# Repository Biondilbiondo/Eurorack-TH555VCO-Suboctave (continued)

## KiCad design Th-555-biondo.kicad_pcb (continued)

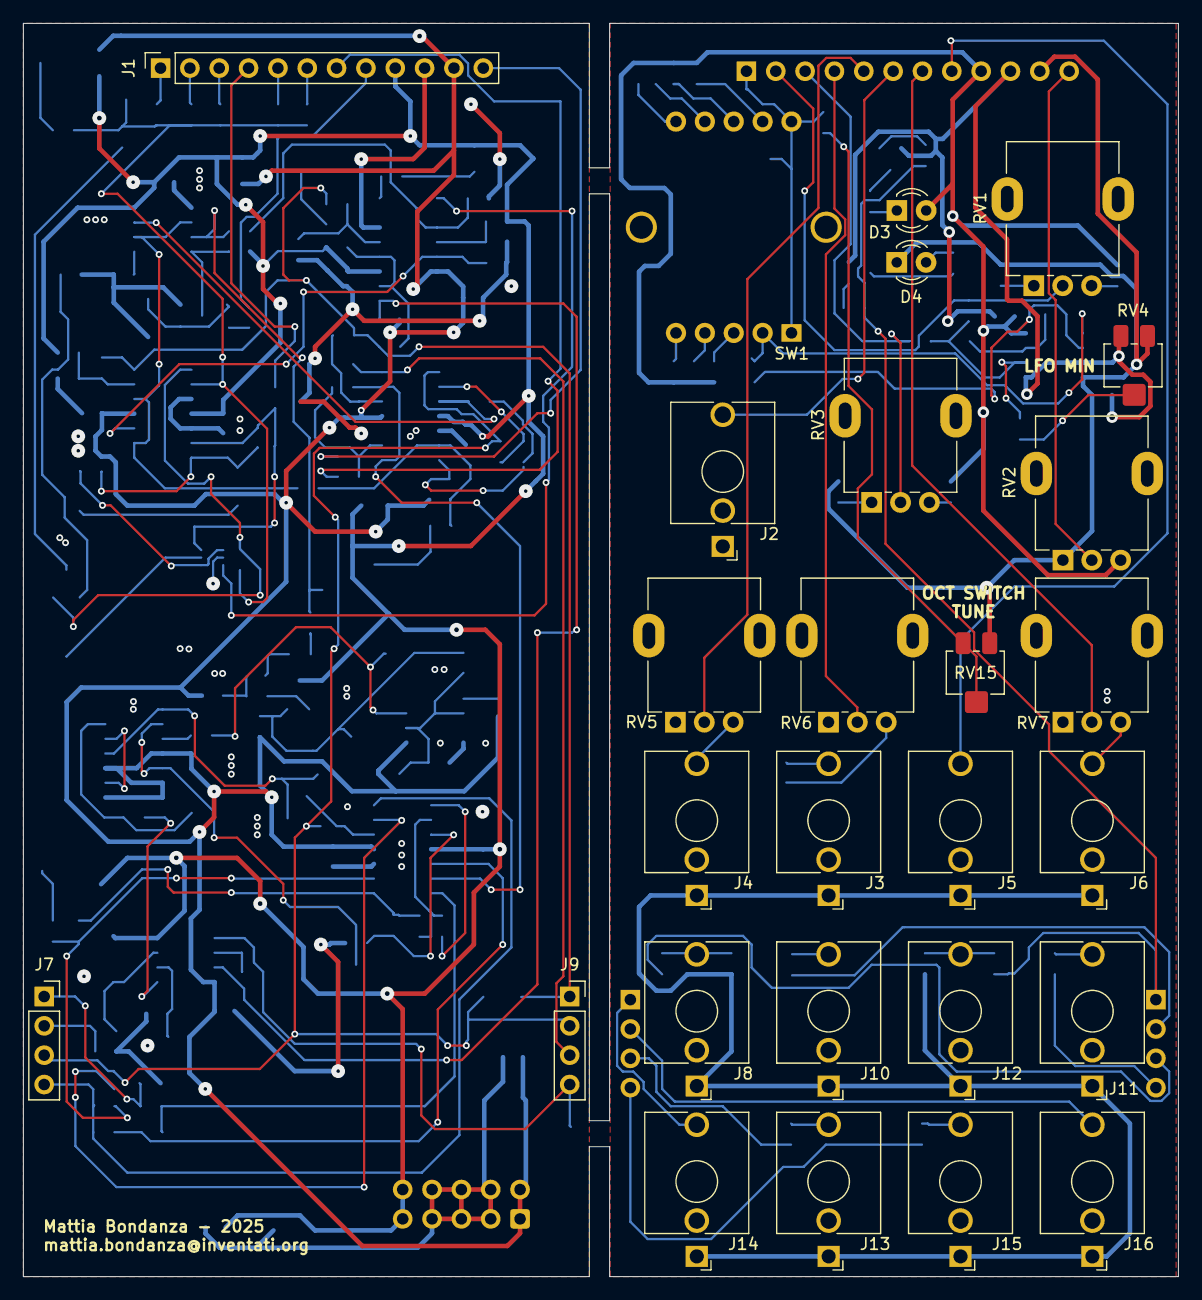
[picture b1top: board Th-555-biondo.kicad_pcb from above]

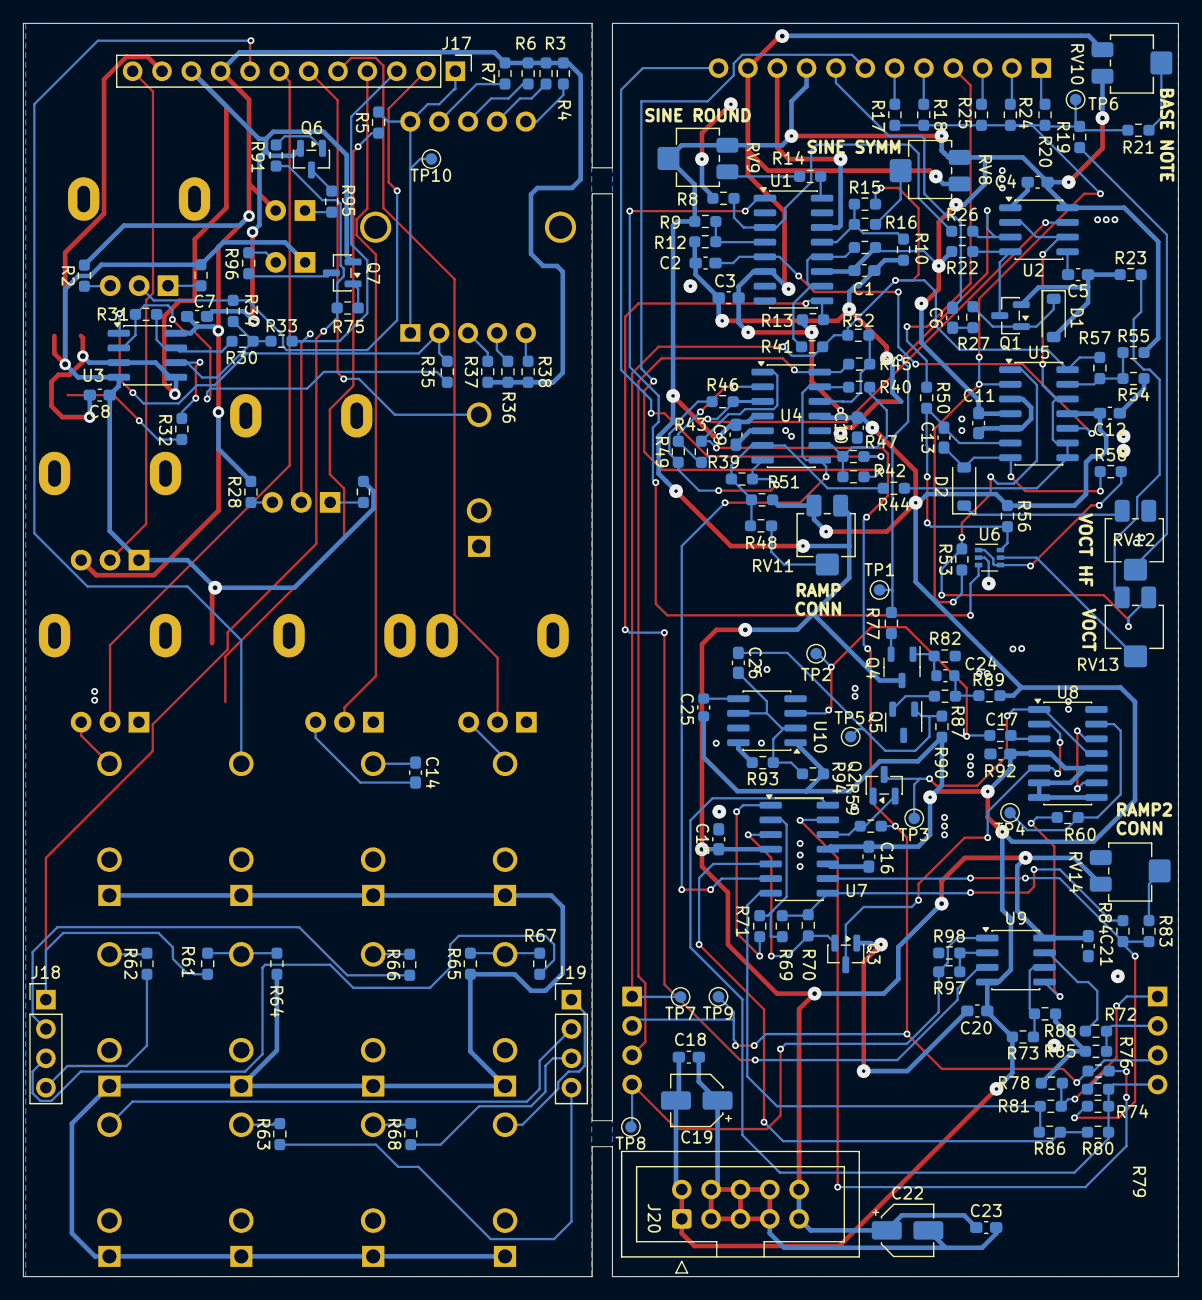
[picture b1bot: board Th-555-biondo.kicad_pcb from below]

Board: 2 copper layers, 100.0 x 108.5 mm, 191 parts (164 on the bottom side), 133 nets.

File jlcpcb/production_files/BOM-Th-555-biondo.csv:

Comment,Designator,Footprint,LCSC,Quantity
100n,C20,C_0603_1608Metric_Pad1.08x0.95mm_HandSolder,,1
100n,C8,C_0603_1608Metric_Pad1.08x0.95mm_HandSolder,,1
100k,R71,R_0603_1608Metric_Pad0.98x0.95mm_HandSolder,,1
100k,R93,R_0603_1608Metric_Pad0.98x0.95mm_HandSolder,,1
Conn_01x04,J18,PinHeader_1x04_P2.54mm_Vertical,,1
100k,R76,R_0603_1608Metric_Pad0.98x0.95mm_HandSolder,,1
7.15k,R6,R_0603_1608Metric_Pad0.98x0.95mm_HandSolder,,1
100k,RV11,Potentiometer_Bourns_3214X_Vertical,,1
10k,R75,R_0603_1608Metric_Pad0.98x0.95mm_HandSolder,,1
100k,R25,R_0603_1608Metric_Pad0.98x0.95mm_HandSolder,,1
100R,RV13,Potentiometer_Bourns_3214X_Vertical,,1
11.8k,R38,R_0603_1608Metric_Pad0.98x0.95mm_HandSolder,,1
7.15k,R5,R_0603_1608Metric_Pad0.98x0.95mm_HandSolder,,1
10k,R90,R_0603_1608Metric_Pad0.98x0.95mm_HandSolder,,1
100k,R69,R_0603_1608Metric_Pad0.98x0.95mm_HandSolder,,1
1.5M,R56,R_0603_1608Metric_Pad0.98x0.95mm_HandSolder,,1
10u,C22,CP_Elec_4x5.8,,1
1n,C24,C_0603_1608Metric,,1
100k,R79,R_0603_1608Metric_Pad0.98x0.95mm_HandSolder,,1
1k,R96,R_0603_1608Metric_Pad0.98x0.95mm_HandSolder,,1
2.2k,R80,R_0603_1608Metric_Pad0.98x0.95mm_HandSolder,,1
150k,R51,R_0603_1608Metric_Pad0.98x0.95mm_HandSolder,,1
10k,R55,R_0603_1608Metric_Pad0.98x0.95mm_HandSolder,,1
100k,R70,R_0603_1608Metric_Pad0.98x0.95mm_HandSolder,,1
100n,C15,C_0603_1608Metric_Pad1.08x0.95mm_HandSolder,,1
1.5k,R12,R_0603_1608Metric_Pad0.98x0.95mm_HandSolder,,1
100k,R98,R_0603_1608Metric_Pad0.98x0.95mm_HandSolder,,1
1M,R48,R_0603_1608Metric_Pad0.98x0.95mm_HandSolder,,1
100k,R88,R_0603_1608Metric_Pad0.98x0.95mm_HandSolder,,1
TL072,U3,SOIC-8_3.9x4.9mm_P1.27mm,,1
4.7k,R22,R_0603_1608Metric_Pad0.98x0.95mm_HandSolder,,1
2k +3500ppm/K,R53,R_0603_1608Metric_Pad0.98x0.95mm_HandSolder,,1
200k,R30,R_0603_1608Metric_Pad0.98x0.95mm_HandSolder,,1
220n,C14,C_0603_1608Metric_Pad1.08x0.95mm_HandSolder,,1
100n,C17,C_0603_1608Metric_Pad1.08x0.95mm_HandSolder,,1
390R,R10,R_0603_1608Metric_Pad0.98x0.95mm_HandSolder,,1
5.6k,R13,R_0603_1608Metric_Pad0.98x0.95mm_HandSolder,,1
Conn_02x05_Odd_Even,J20,IDC-Header_2x05_P2.54mm_Vertical,,1
1M,R19,R_0603_1608Metric_Pad0.98x0.95mm_HandSolder,,1
100n,C9,C_0603_1608Metric_Pad1.08x0.95mm_HandSolder,,1
1k,R61,R_0603_1608Metric_Pad0.98x0.95mm_HandSolder,,1
100k,R83,R_0603_1608Metric_Pad0.98x0.95mm_HandSolder,,1
237k,R29,R_0603_1608Metric_Pad0.98x0.95mm_HandSolder,,1
20k,R54,R_0603_1608Metric_Pad0.98x0.95mm_HandSolder,,1
100k,R59,R_0603_1608Metric_Pad0.98x0.95mm_HandSolder,,1
10k,R89,R_0603_1608Metric_Pad0.98x0.95mm_HandSolder,,1
10k,R49,R_0603_1608Metric_Pad0.98x0.95mm_HandSolder,,1
TL074,U7,SOIC-14_3.9x8.7mm_P1.27mm,,1
TL072,U9,SOIC-8_3.9x4.9mm_P1.27mm,,1
25k,R2,R_0603_1608Metric_Pad0.98x0.95mm_HandSolder,,1
47k,R94,R_0603_1608Metric_Pad0.98x0.95mm_HandSolder,,1
2.2k,R52,R_0603_1608Metric_Pad0.98x0.95mm_HandSolder,,1
10k,R91,R_0603_1608Metric_Pad0.98x0.95mm_HandSolder,,1
100k,R73,R_0603_1608Metric_Pad0.98x0.95mm_HandSolder,,1
1k,R95,R_0603_1608Metric_Pad0.98x0.95mm_HandSolder,,1
10.0k,R4,R_0603_1608Metric_Pad0.98x0.95mm_HandSolder,,1
1k,R65,R_0603_1608Metric_Pad0.98x0.95mm_HandSolder,,1
100n,C7,C_0603_1608Metric_Pad1.08x0.95mm_HandSolder,,1
1n,C5,C_0603_1608Metric_Pad1.08x0.95mm_HandSolder,,1
100k,R97,R_0603_1608Metric_Pad0.98x0.95mm_HandSolder,,1
100k,R34,R_0603_1608Metric_Pad0.98x0.95mm_HandSolder,,1
100p,C13,C_0603_1608Metric_Pad1.08x0.95mm_HandSolder,,1
100n,C10,C_0603_1608Metric_Pad1.08x0.95mm_HandSolder,,1
100n,C18,C_0603_1608Metric_Pad1.08x0.95mm_HandSolder,,1
100k,R15,R_0603_1608Metric_Pad0.98x0.95mm_HandSolder,,1
1M,R50,R_0603_1608Metric_Pad0.98x0.95mm_HandSolder,,1
100k,R74,R_0603_1608Metric_Pad0.98x0.95mm_HandSolder,,1
100k,R24,R_0603_1608Metric_Pad0.98x0.95mm_HandSolder,,1
TL074,U5,SOIC-14_3.9x8.7mm_P1.27mm,,1
MMBT3904,Q1,SOT-23,,1
4.7k,R26,R_0603_1608Metric_Pad0.98x0.95mm_HandSolder,,1
10k,R35,R_0603_1608Metric_Pad0.98x0.95mm_HandSolder,,1
100n,C1,C_0603_1608Metric_Pad1.08x0.95mm_HandSolder,,1
1k,R63,R_0603_1608Metric_Pad0.98x0.95mm_HandSolder,,1
237k,R28,R_0603_1608Metric_Pad0.98x0.95mm_HandSolder,,1
100k,R27,R_0603_1608Metric_Pad0.98x0.95mm_HandSolder,,1
100k,R17,R_0603_1608Metric_Pad0.98x0.95mm_HandSolder,,1
22k,R58,R_0603_1608Metric_Pad0.98x0.95mm_HandSolder,,1
10k,R77,R_0603_1608Metric_Pad0.98x0.95mm_HandSolder,,1
MMBT3906,Q7,SOT-23,,1
10k,R43,R_0603_1608Metric_Pad0.98x0.95mm_HandSolder,,1
100k,R60,R_0603_1608Metric_Pad0.98x0.95mm_HandSolder,,1
100k,RV8,Potentiometer_Bourns_3214X_Vertical,,1
14.0k,R36,R_0603_1608Metric_Pad0.98x0.95mm_HandSolder,,1
470p,C6,C_0603_1608Metric_Pad1.08x0.95mm_HandSolder,,1
10n,C25,C_0603_1608Metric,,1
2200pF C0G/NP0,C2,C_0603_1608Metric_Pad1.08x0.95mm_HandSolder,,1
10k,R9,R_0603_1608Metric_Pad0.98x0.95mm_HandSolder,,1
1.5k,R8,R_0603_1608Metric_Pad0.98x0.95mm_HandSolder,,1
100k,R18,R_0603_1608Metric_Pad0.98x0.95mm_HandSolder,,1
10k,R82,R_0603_1608Metric_Pad0.98x0.95mm_HandSolder,,1
MMBT3904,Q6,SOT-23,,1
100n,C11,C_0603_1608Metric_Pad1.08x0.95mm_HandSolder,,1
10u,C19,CP_Elec_4x5.8,,1
100k,R20,R_0603_1608Metric_Pad0.98x0.95mm_HandSolder,,1
LM13700,U1,SOIC-16_3.9x9.9mm_P1.27mm,,1
100n,C21,C_0603_1608Metric_Pad1.08x0.95mm_HandSolder,,1
1N4148W,D2,D_SOD-123,,1
1M,R16,R_0603_1608Metric_Pad0.98x0.95mm_HandSolder,,1
6.04k,R7,R_0603_1608Metric_Pad0.98x0.95mm_HandSolder,,1
10k,R31,R_0603_1608Metric_Pad0.98x0.95mm_HandSolder,,1
25k,RV9,Potentiometer_Bourns_3214X_Vertical,,1
2.2M,R86,R_0603_1608Metric_Pad0.98x0.95mm_HandSolder,,1
100n,C4,C_0603_1608Metric_Pad1.08x0.95mm_HandSolder,,1
100n,C3,C_0603_1608Metric_Pad1.08x0.95mm_HandSolder,,1
22k,R14,R_0603_1608Metric_Pad0.98x0.95mm_HandSolder,,1
4013,U8,SOIC-14_3.9x8.7mm_P1.27mm,,1
MMBT3904,Q5,SOT-23-3_npn,,1
100k,R21,R_0603_1608Metric_Pad0.98x0.95mm_HandSolder,,1
8.45k,R3,R_0603_1608Metric_Pad0.98x0.95mm_HandSolder,,1
330k,R47,R_0603_1608Metric_Pad0.98x0.95mm_HandSolder,,1
ICM7555xB,U2,SOIC-8_3.9x4.9mm_P1.27mm,,1
1k,R62,R_0603_1608Metric_Pad0.98x0.95mm_HandSolder,,1
10k,R87,R_0603_1608Metric_Pad0.98x0.95mm_HandSolder,,1
100k,RV14,Potentiometer_Bourns_3214X_Vertical,,1
300k,R11,R_0603_1608Metric_Pad0.98x0.95mm_HandSolder,,1
2.2k,R85,R_0603_1608Metric_Pad0.98x0.95mm_HandSolder,,1
1k,R68,R_0603_1608Metric_Pad0.98x0.95mm_HandSolder,,1
51k,R84,R_0603_1608Metric_Pad0.98x0.95mm_HandSolder,,1
1k,R64,R_0603_1608Metric_Pad0.98x0.95mm_HandSolder,,1
10k,R46,R_0603_1608Metric_Pad0.98x0.95mm_HandSolder,,1
BCM857BS,U6,SOT-363_SC-70-6,,1
2.2M,R45,R_0603_1608Metric_Pad0.98x0.95mm_HandSolder,,1
200k,R32,R_0603_1608Metric_Pad0.98x0.95mm_HandSolder,,1
TL074,U4,SOIC-14_3.9x8.7mm_P1.27mm,,1
1k,R67,R_0603_1608Metric_Pad0.98x0.95mm_HandSolder,,1
1N4148W,D1,D_SOD-123,,1
1k,R66,R_0603_1608Metric_Pad0.98x0.95mm_HandSolder,,1
100k,RV12,Potentiometer_Bourns_3214X_Vertical,,1
100n,C12,C_0603_1608Metric_Pad1.08x0.95mm_HandSolder,,1
10k,R92,R_0603_1608Metric_Pad0.98x0.95mm_HandSolder,,1
MMBF4391,Q3,SOT-23,,1
3k,R81,R_0603_1608Metric_Pad0.98x0.95mm_HandSolder,,1
390R,R23,R_0603_1608Metric_Pad0.98x0.95mm_HandSolder,,1
Conn_01x12,J17,PinHeader_1x12_P2.54mm_Vertical,,1
2.2k,R78,R_0603_1608Metric_Pad0.98x0.95mm_HandSolder,,1
100k,R44,R_0603_1608Metric_Pad0.98x0.95mm_HandSolder,,1
MMBF4391,Q2,SOT-23,,1
16.5k,R37,R_0603_1608Metric_Pad0.98x0.95mm_HandSolder,,1
100k,R42,R_0603_1608Metric_Pad0.98x0.95mm_HandSolder,,1
Conn_01x04,J19,PinHeader_1x04_P2.54mm_Vertical,,1
10k,RV10,Potentiometer_Bourns_3214X_Vertical,,1
2k,R72,R_0603_1608Metric_Pad0.98x0.95mm_HandSolder,,1
20k,R57,R_0603_1608Metric_Pad0.98x0.95mm_HandSolder,,1
39k,R41,R_0603_1608Metric_Pad0.98x0.95mm_HandSolder,,1
MMBT3904,Q4,SOT-23-3_npn,,1
120k,R40,R_0603_1608Metric_Pad0.98x0.95mm_HandSolder,,1
100n,C16,C_0603_1608Metric_Pad1.08x0.95mm_HandSolder,,1
25k,R1,R_0603_1608Metric_Pad0.98x0.95mm_HandSolder,,1
100k,R33,R_0603_1608Metric_Pad0.98x0.95mm_HandSolder,,1
100n,C23,C_0603_1608Metric_Pad1.08x0.95mm_HandSolder,,1
ICM7555xB,U10,SOIC-8_3.9x4.9mm_P1.27mm,,1
137k,R39,R_0603_1608Metric_Pad0.98x0.95mm_HandSolder,,1
1n,C26,C_0603_1608Metric_Pad1.08x0.95mm_HandSolder,,1

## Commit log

2025-11-21 First commit, this is already version v 0.3
2025-11-21 Added production files
2025-11-21 README.md improved
